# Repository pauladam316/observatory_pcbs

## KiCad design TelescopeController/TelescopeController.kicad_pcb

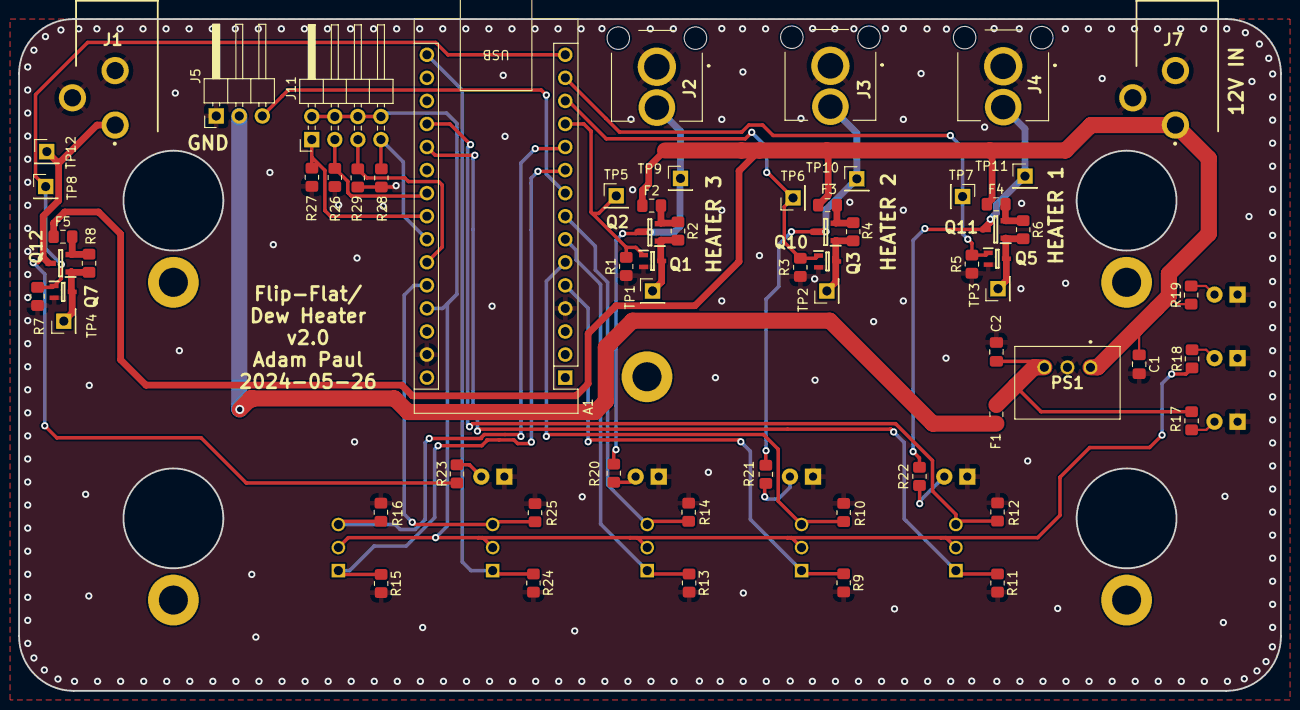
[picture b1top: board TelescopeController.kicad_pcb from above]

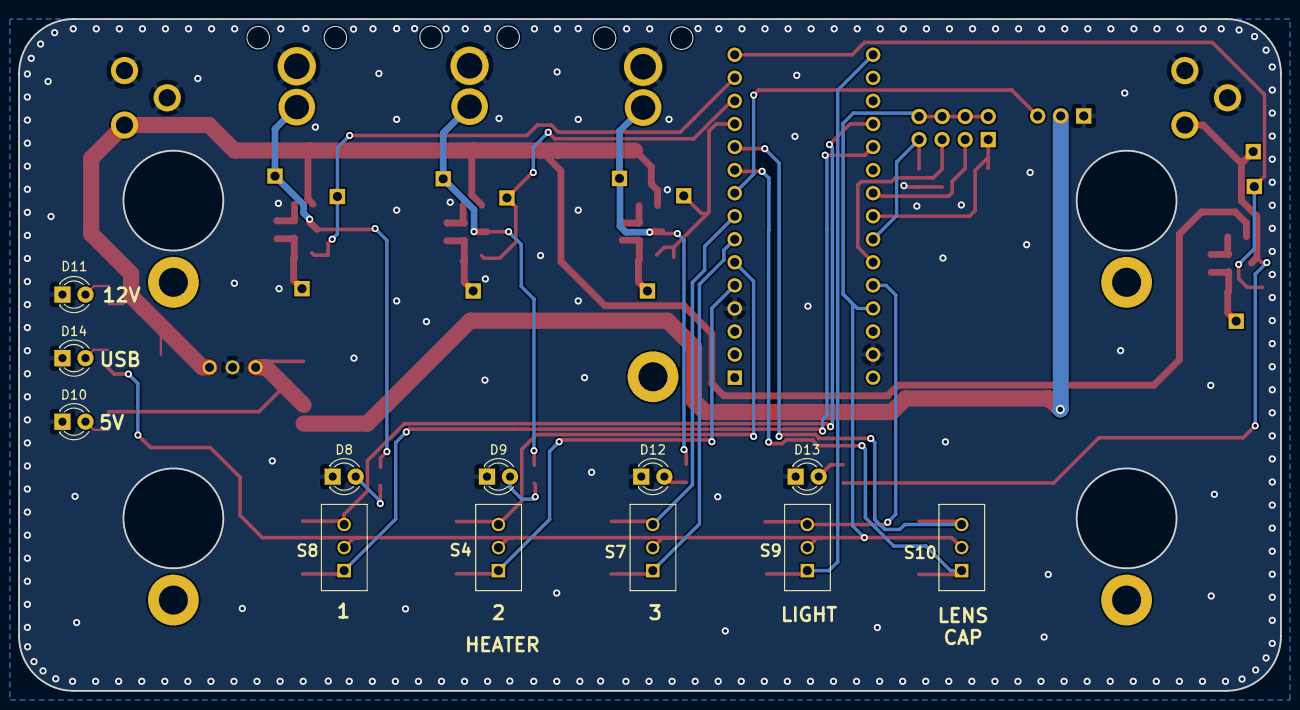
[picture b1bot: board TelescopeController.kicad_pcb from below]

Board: 2 copper layers, 139.0 x 74.0 mm, 77 parts (12 on the bottom side), 43 nets.

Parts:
A1: Arduino_Nano_v3.x; Arduino_Nano
C1: 10uF; C_0805_2012Metric_Pad1.18x1.45mm_HandSolder
C2: 22uF; C_0805_2012Metric_Pad1.18x1.45mm_HandSolder
D8, D9, D10, D11, D12, D13, D14: LED; LED_D3.0mm
F1: 1A; Fuse_0805_2012Metric_Pad1.15x1.40mm_HandSolder
F2, F3, F4, F5: 1.5A; Fuse_0805_2012Metric_Pad1.15x1.40mm_HandSolder
J1, J7: PJ-102BH; PJ-102AH
J2, J3, J4: RCJ-041; RCJ041
J5: Conn_01x03_Pin; PinHeader_1x03_P2.54mm_Horizontal
J11: Conn_02x04_Counter_Clockwise; PinHeader_2x04_P2.54mm_Horizontal
PS1: P78E05-1000; P78E051000
Q1, Q3, Q5, Q7: DMN63D8LW-13; SOT65P210X110-3N
Q2, Q10, Q11, Q12: DMP3099L-7; SOT96P240X115-3N
R1, R2, R3, R4, R5, R6, R7, R8, R9, R10, R11, R12, R13, R14, R15, R16, R19, R20, R21, R22, R23, R24, R25: 1k; R_0805_2012Metric_Pad1.20x1.40mm_HandSolder
R17, R18: 300R; R_0805_2012Metric_Pad1.20x1.40mm_HandSolder
R26, R27, R28, R29: 10k; R_0805_2012Metric_Pad1.20x1.40mm_HandSolder
S4, S7, S8, S9, S10: AS1E-2M-10-Z; AS1E2M10Z
TP1, TP2, TP3, TP4, TP5, TP6, TP7, TP8, TP9, TP10, TP11, TP12: TestPoint; PinHeader_1x01_P2.54mm_Vertical

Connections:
+5V: A1.27 (+5V), J11.2, J11.4, J11.6, J11.8, R18.1, S4.2, S7.2, S8.2, S9.2, S10.2
+12V: C1.1, F2.1, F3.1, F4.1, F5.1, J7.1, PS1.1 (+VIN), R19.1
/12V_SWITCHING1/IN: A1.13 (D10), Q3.1, R3.1, TP6.1
/12V_SWITCHING1/OUT: J3.2, Q10.3 (D), R21.1, TP10.1
/12V_SWITCHING2/IN: A1.14 (D11), Q5.1, R5.1, TP7.1
/12V_SWITCHING2/OUT: J4.2, Q11.3 (D), R22.1, TP11.1
/12V_SWITCHING3/IN: A1.15 (D12), Q7.1, R7.1, TP8.1
/12V_SWITCHING3/OUT: J1.1, Q12.3 (D), R23.1, TP12.1
/12V_SWITCHING/IN: A1.12 (D9), Q1.1, R1.1, TP5.1
/12V_SWITCHING/OUT: J2.2, Q2.3 (D), R20.1, TP9.1
/CAP_CLOSE: A1.11 (D8), R16.1, S10.3
/CAP_OPEN: A1.10 (D7), R15.1, S10.1
/HEATER1_OFF: A1.19 (A0), R12.1, S8.3
/HEATER1_ON: A1.20 (A1), R11.1, S8.1
/HEATER2_OFF: A1.6 (D3), R10.1, S4.3
/HEATER2_ON: A1.5 (D2), R9.1, S4.1
/HEATER3_OFF: A1.8 (D5), R14.1, S7.3
/HEATER3_ON: A1.7 (D4), R13.1, S7.1
/LIGHT_OFF: A1.26 (A7), R25.1, S9.3
/LIGHT_ON: A1.16 (D13), R24.1, S9.1
/Thermistor1/AOUT: A1.23 (A4), J11.1, R27.1
/Thermistor2/AOUT: A1.24 (A5), J11.7, R28.1
/Thermistor3/AOUT: A1.25 (A6), J11.5, R29.1
/Thermistor/AOUT: A1.22 (A3), J11.3, R26.1
GND: A1.4 (GND), A1.29 (GND), C1.2, C2.2, D8.1 (K), D9.1 (K), D10.1 (K), D11.1 (K), D12.1 (K), D13.1 (K), D14.1 (K), J1.2, J1.3, J2.1, J3.1, J4.1, J5.1, J7.2, J7.3, PS1.2 (GND), Q1.2, Q3.2, Q5.2, Q7.2, R1.2, R3.2, R5.2, R7.2, R9.2, R10.2, R11.2, R12.2, R13.2, R14.2, R15.2, R16.2, R24.2, R25.2, R26.2, R27.2, R28.2, R29.2
unnamed: A1.9 (D6), J5.3
unnamed: D8.2 (A), R22.2
unnamed: D9.2 (A), R21.2
unnamed: D10.2 (A), R17.2
unnamed: D11.2 (A), R19.2
unnamed: D12.2 (A), R20.2
unnamed: D13.2 (A), R23.2
unnamed: D14.2 (A), R18.2
unnamed: F1.2, J5.2
unnamed: C2.1, F1.1, PS1.3 (+VOUT), R17.1
unnamed: Q1.3, Q2.1 (G), R2.2, TP1.1
unnamed: F2.2, Q2.2 (S), R2.1
unnamed: Q3.3, Q10.1 (G), R4.2, TP2.1
unnamed: F3.2, Q10.2 (S), R4.1
unnamed: Q5.3, Q11.1 (G), R6.2, TP3.1
unnamed: F4.2, Q11.2 (S), R6.1
unnamed: Q7.3, Q12.1 (G), R8.2, TP4.1
unnamed: F5.2, Q12.2 (S), R8.1

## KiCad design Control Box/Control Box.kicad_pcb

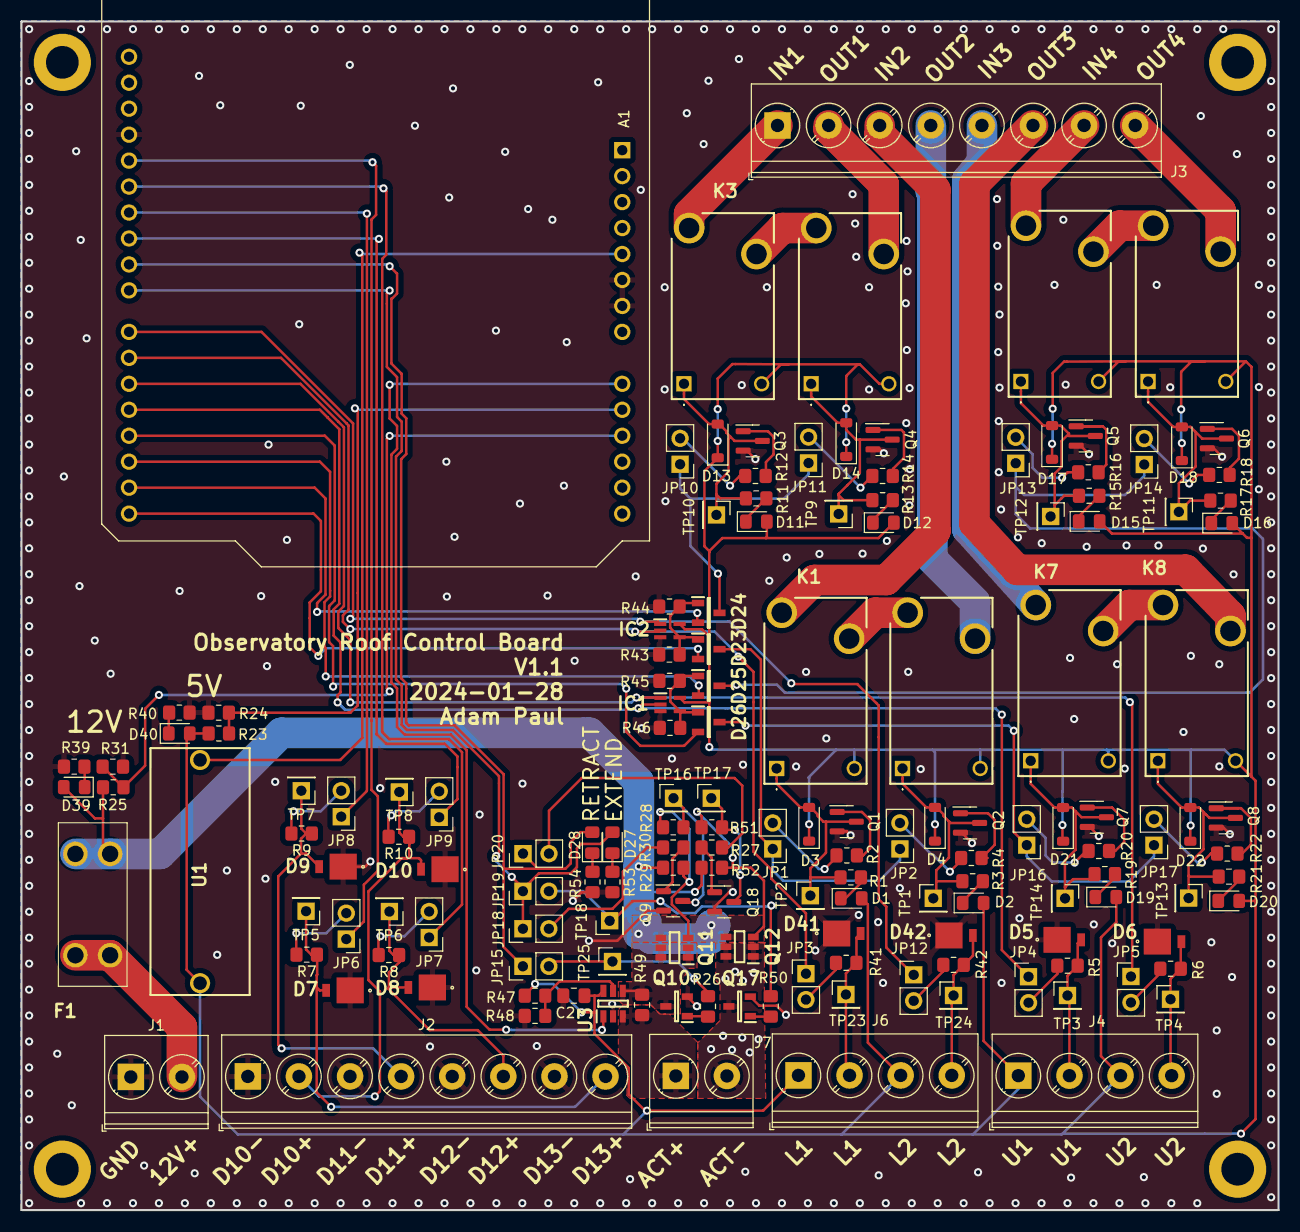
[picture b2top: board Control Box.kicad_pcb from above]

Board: 2 copper layers, 123.0 x 116.3 mm, 158 parts (0 on the bottom side), 108 nets.

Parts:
A1: Arduino_UNO_R3
C2: 0.1uF; C_0805_2012Metric_Pad1.18x1.45mm_HandSolder
D1, D2, D11, D12, D15, D16, D19, D20, D27, D28, D39, D40: LG R971-KN-1; LED_0805_2012Metric_Pad1.15x1.40mm_HandSolder
D3, D4, D13, D14, D17, D18, D21, D22: 1N4148W-TP; D_SOD-123
D5, D6, D7, D8, D9, D10, D41, D42: SMP5.0A-M3/84A; DO-220AA
D23, D24, D25, D26: DMG2305UX-13; SOT96P240X120-3N
F1: 3568
H1, H2, H3, H4: MountingHole; MountingHole_3.2mm_M3_DIN965_Pad
IC1, IC2: SN74LVC1G32DCKR; SOT65P210X110-5N
J1, J7: Screw_Terminal_01x02; TerminalBlock_Phoenix_PT-1,5-2-5.0-H_1x02_P5.00mm_Horizontal
J2, J3: Screw_Terminal_01x08; TerminalBlock_Phoenix_PT-1,5-8-5.0-H_1x08_P5.00mm_Horizontal
J4, J6: Screw_Terminal_01x04; TerminalBlock_Phoenix_PT-1,5-4-5.0-H_1x04_P5.00mm_Horizontal
JP1, JP2, JP3, JP4, JP5, JP6, JP7, JP8, JP9, JP10, JP11, JP12, JP13, JP14, JP15, JP16, JP17, JP18, JP19, JP20: Jumper; PinHeader_1x02_P2.54mm_Vertical
K1, K2, K3, K4, K5, K6, K7, K8: AHQSH105LM100G
Q1, Q2, Q3, Q4, Q5, Q6, Q7, Q8, Q9, Q18: MMBT3904; SOT-23
Q10, Q17: DMN2056U-7; SOT96P240X100-3N
Q11, Q12: SI3443CDV-T1-GE3; SOP95P284X110-6N
R1, R3, R11, R13, R15, R17, R19, R21, R40, R53, R54: 140R; R_0805_2012Metric_Pad1.20x1.40mm_HandSolder
R2, R4, R12, R14, R16, R18, R20, R22: 500R; R_0805_2012Metric_Pad1.20x1.40mm_HandSolder
R5, R6, R7, R8, R9, R10, R41, R42: 125R; R_0805_2012Metric_Pad1.20x1.40mm_HandSolder
R23, R24, R25, R47, R48: 10k; R_0805_2012Metric_Pad1.20x1.40mm_HandSolder
R26, R28, R43, R44, R45, R46, R50, R51: 1k; R_0805_2012Metric_Pad1.20x1.40mm_HandSolder
R27, R30: 2.2k; R_0805_2012Metric_Pad1.20x1.40mm_HandSolder
R29, R52: 4.7k; R_0805_2012Metric_Pad1.20x1.40mm_HandSolder
R31: 3k; R_0805_2012Metric_Pad1.20x1.40mm_HandSolder
R39: 490R; R_0805_2012Metric_Pad1.20x1.40mm_HandSolder
R49: 42m; R_0805_2012Metric_Pad1.20x1.40mm_HandSolder
TP1, TP2, TP3, TP4, TP5, TP6, TP7, TP8, TP9, TP10, TP11, TP12, TP13, TP14, TP16, TP17, TP18, TP23, TP24, TP25: TestPoint; PinHeader_1x01_P2.54mm_Vertical
U1: 4527
U3: INA181A1IDBVR; SOT95P280X145-6N

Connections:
+5V: C2.1, D1.2 (A), D2.2 (A), D3.1 (K), D4.1 (K), D11.2 (A), D12.2 (A), D13.1 (K), D14.1 (K), D15.2 (A), D16.2 (A), D17.1 (K), D18.1 (K), D19.2 (A), D20.2 (A), D21.1 (K), D22.1 (K), D40.2 (A), IC1.5 (VCC), IC2.5 (VCC), J4.1, J4.3, J6.1, J6.3, K1.2 (COIL_2), K2.2 (COIL_2), K3.2 (COIL_2), K4.2 (COIL_2), K5.2 (COIL_2), K6.2 (COIL_2), K7.2 (COIL_2), K8.2 (COIL_2), R23.2, R47.1, U1.1, U3.6 (VS)
+12V: D39.2 (A), F1.3, F1.4, Q11.4 (S), Q12.4 (S), R25.2, R29.2, R52.2
/GPIOProtection1/IN: A1.21 (D6), IC2.2 (B), JP3.1
/GPIOProtection1/OUT: D41.2, J6.2, R41.1, TP23.1
/GPIOProtection/IN: A1.19 (D4), IC1.2 (B), JP4.1
/GPIOProtection/OUT: D5.2, J4.2, R5.1, TP3.1
/H-Bridge/+OUT: J7.1, R49.2, U3.3 (IN+)
/H-Bridge/-OUT: J7.2, Q12.1 (D_1), Q12.2 (D_2), Q12.5 (D_3), Q12.6 (D_4), Q17.3 (D)
/H-Bridge/EXTEND: A1.23 (D8), D27.2 (A), JP18.1, JP19.1
/H-Bridge/RETRACT: A1.24 (D9), D28.2 (A), JP15.1, JP20.1
/H-Bridge/SENSE: A1.9 (A0), U3.1 (OUT)
/OR GATE1/A: A1.22 (D7), IC2.1 (A), JP12.1
/OR GATE1/Y: D23.1 (G), D24.1 (G), IC2.4 (Y), R43.1, R44.1
/OR GATE/A: A1.20 (D5), IC1.1 (A), JP5.1
/OR GATE/Y: D25.1 (G), D26.1 (G), IC1.4 (Y), R45.1, R46.1
/Relay/EN: A1.15 (D0/RX), D23.2 (S)
/Relay/IN: J3.3, K1.4 (NO)
/Relay/OUT: J3.4, K2.3 (COM)
/sheet651C9752/OUT: D6.2, J4.4, R6.1, TP4.1
/sheet651C9753/OUT: D42.2, J6.4, R42.1, TP24.1
/sheet652FCB77/EN: A1.16 (D1/TX), D24.2 (S)
/sheet652FCB77/IN: J3.1, K3.4 (NO)
/sheet652FCB77/OUT: J3.2, K4.3 (COM)
/sheet6528B80B/IN: A1.25 (D10), JP9.1
/sheet6528B80B/OUT: D10.2, J2.2, R10.1, TP8.1
/sheet65287DBB/IN: A1.26 (D11), JP8.1
/sheet65287DBB/OUT: D9.2, J2.4, R9.1, TP7.1
/sheet65300B6A/EN: A1.17 (D2), D25.2 (S)
/sheet65300B6A/IN: J3.7, K5.4 (NO)
/sheet65300B6A/OUT: J3.8, K6.3 (COM)
/sheet65304B89/EN: A1.18 (D3), D26.2 (S)
/sheet65304B89/IN: J3.5, K7.4 (NO)
/sheet65304B89/OUT: J3.6, K8.3 (COM)
/sheet652808C1/IN: A1.28 (D13), JP6.1
/sheet652808C1/OUT: D7.2, J2.8, R7.1, TP5.1
/sheet65284368/IN: A1.27 (D12), JP7.1
/sheet65284368/OUT: D8.2, J2.6, R8.1, TP6.1
GND: A1.6 (GND), A1.7 (GND), A1.29 (GND), C2.2, D5.1, D6.1, D7.1, D8.1, D9.1, D10.1, D41.1, D42.1, IC1.3 (GND), IC2.3 (GND), J1.1, J2.1, J2.3, J2.5, J2.7, Q1.2 (E), Q2.2 (E), Q3.2 (E), Q4.2 (E), Q5.2 (E), Q6.2 (E), Q7.2 (E), Q8.2 (E), Q9.2 (E), Q10.2 (S), Q17.2 (S), Q18.2 (E), R24.1, R31.1, R39.2, R40.2, R43.2, R44.2, R45.2, R46.2, R48.2, R53.2, R54.2, U3.2 (GND)
unnamed: A1.5 (+5V), U1.2
unnamed: A1.10 (A1), R23.1, R24.2
unnamed: A1.11 (A2), R25.1, R31.2
unnamed: D1.1 (K), R1.1
unnamed: D2.1 (K), R3.1
unnamed: D3.2 (A), K1.1 (COIL_1), Q1.3 (C), R1.2, TP2.1
unnamed: D4.2 (A), K2.1 (COIL_1), Q2.3 (C), R3.2, TP1.1
unnamed: D11.1 (K), R11.1
unnamed: D12.1 (K), R13.1
unnamed: D13.2 (A), K3.1 (COIL_1), Q3.3 (C), R11.2, TP10.1
unnamed: D14.2 (A), K4.1 (COIL_1), Q4.3 (C), R13.2, TP9.1
unnamed: D15.1 (K), R15.1
unnamed: D16.1 (K), R17.1
unnamed: D17.2 (A), K5.1 (COIL_1), Q5.3 (C), R15.2, TP12.1
unnamed: D18.2 (A), K6.1 (COIL_1), Q6.3 (C), R17.2, TP11.1
unnamed: D19.1 (K), R19.1
unnamed: D20.1 (K), R21.1
unnamed: D21.2 (A), K7.1 (COIL_1), Q7.3 (C), R19.2, TP14.1
unnamed: D22.2 (A), K8.1 (COIL_1), Q8.3 (C), R21.2, TP13.1
unnamed: D23.3 (D), JP1.1, JP2.1
unnamed: D24.3 (D), JP10.1, JP11.1
unnamed: D25.3 (D), JP13.1, JP14.1
unnamed: D26.3 (D), JP16.1, JP17.1
unnamed: D27.1 (K), R53.1
unnamed: D28.1 (K), R54.1
unnamed: D39.1 (K), R39.1
unnamed: D40.1 (K), R40.1
unnamed: F1.1, F1.2, J1.2
unnamed: JP1.2, R2.2
unnamed: JP2.2, R4.2
unnamed: JP3.2, R41.2
unnamed: JP4.2, R5.2
unnamed: JP5.2, R6.2
unnamed: JP6.2, R7.2
unnamed: JP7.2, R8.2
unnamed: JP8.2, R9.2
unnamed: JP9.2, R10.2
unnamed: JP10.2, R12.2
unnamed: JP11.2, R14.2
unnamed: JP12.2, R42.2
unnamed: JP13.2, R16.2
unnamed: JP14.2, R18.2
unnamed: JP15.2, R26.2, TP25.1
unnamed: JP16.2, R20.2
unnamed: JP17.2, R22.2
unnamed: JP18.2, R30.2
unnamed: JP19.2, R50.2, TP18.1
unnamed: JP20.2, R27.2
unnamed: K1.3 (COM), K2.4 (NO)
unnamed: K3.3 (COM), K4.4 (NO)
unnamed: K5.3 (COM), K6.4 (NO)
unnamed: K7.3 (COM), K8.4 (NO)
unnamed: Q1.1 (B), R2.1
unnamed: Q2.1 (B), R4.1
unnamed: Q3.1 (B), R12.1
unnamed: Q4.1 (B), R14.1
unnamed: Q5.1 (B), R16.1
unnamed: Q6.1 (B), R18.1
unnamed: Q7.1 (B), R20.1
unnamed: Q8.1 (B), R22.1
unnamed: Q9.1 (B), R30.1
unnamed: Q9.3 (C), R28.2, TP16.1
unnamed: Q10.3 (D), Q11.1 (D_1), Q11.2 (D_2), Q11.5 (D_3), Q11.6 (D_4), R49.1, U3.4 (IN-)
unnamed: Q10.1 (G), R26.1
unnamed: Q11.3 (G), R28.1, R29.1
unnamed: Q12.3 (G), R51.1, R52.1
unnamed: Q17.1 (G), R50.1
unnamed: Q18.1 (B), R27.1
unnamed: Q18.3 (C), R51.2, TP17.1
unnamed: R47.2, R48.1, U3.5 (REF)

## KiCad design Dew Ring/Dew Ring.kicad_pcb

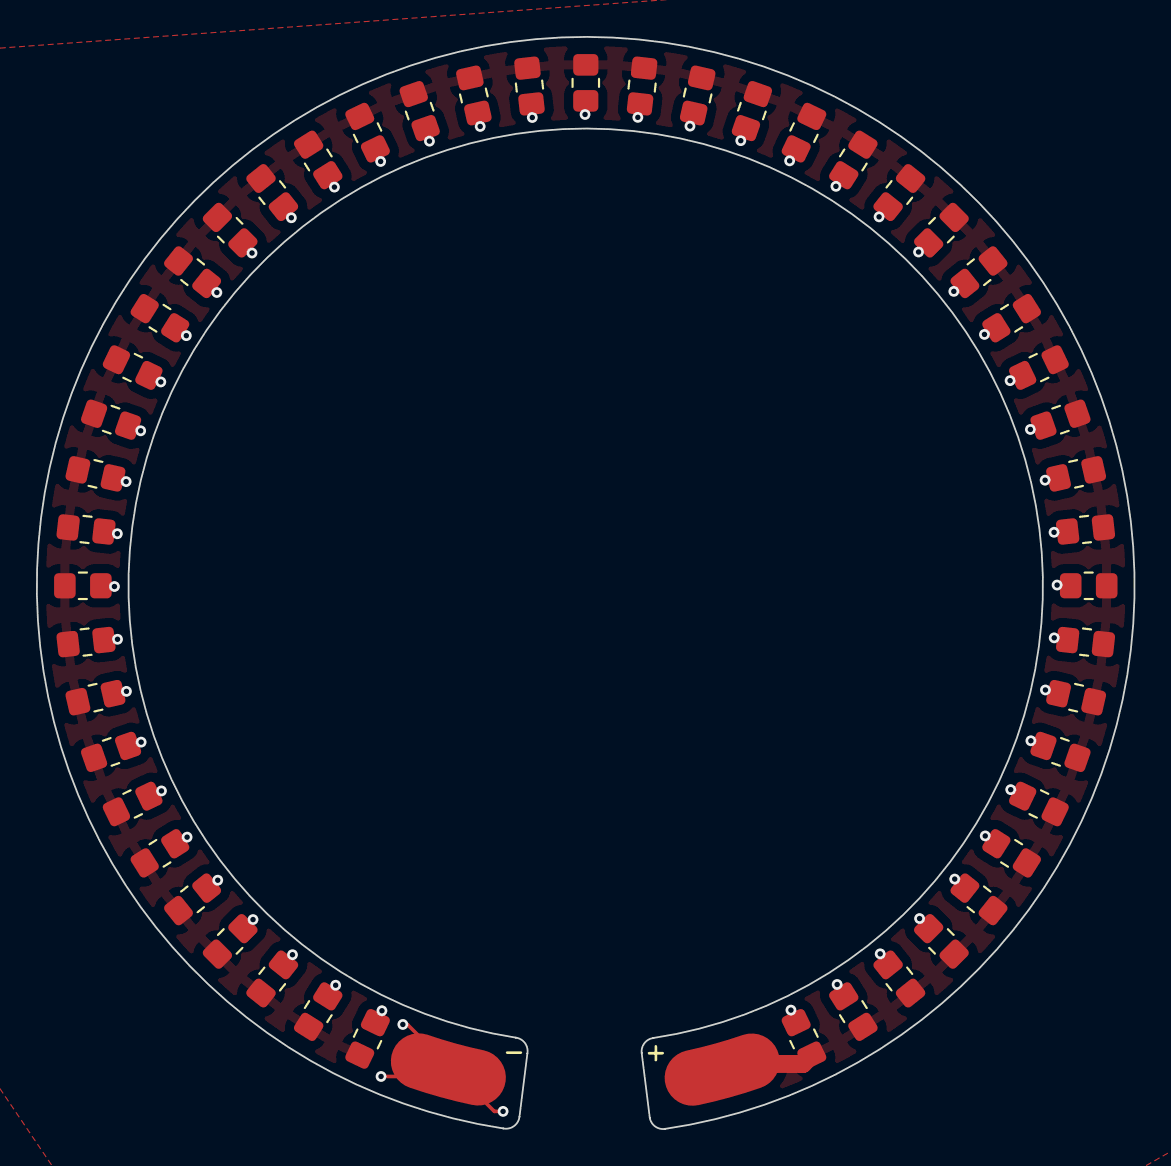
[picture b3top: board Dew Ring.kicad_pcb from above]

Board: 2 copper layers, 61.0 x 60.7 mm, 49 parts (0 on the bottom side), 2 nets.

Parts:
R1, R51, R52, R53, R54, R55, R56, R57, R58, R59, R60, R68, R69, R70, R71, R72, R73, R74, R75, R76, R77, R78, R79, R80, R81, R82, R83, R84, R85, R86, R87, R88, R89, R90, R91, R92, R93, R94, R95, R96, R97, R98, R99, R100, R101, R102, R103, R104, R105: 3.3k; R_0805_2012Metric_Pad1.20x1.40mm_HandSolder

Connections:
+12V: R1.1, R51.1, R52.1, R53.1, R54.1, R55.1, R56.1, R57.1, R58.1, R59.1, R60.1, R68.1, R69.1, R70.1, R71.1, R72.1, R73.1, R74.1, R75.1, R76.1, R77.1, R78.1, R79.1, R80.1, R81.1, R82.1, R83.1, R84.1, R85.1, R86.1, R87.1, R88.1, R89.1, R90.1, R91.1, R92.1, R93.1, R94.1, R95.1, R96.1, R97.1, R98.1, R99.1, R100.1, R101.1, R102.1, R103.1, R104.1, R105.1
GND: R1.2, R51.2, R52.2, R53.2, R54.2, R55.2, R56.2, R57.2, R58.2, R59.2, R60.2, R68.2, R69.2, R70.2, R71.2, R72.2, R73.2, R74.2, R75.2, R76.2, R77.2, R78.2, R79.2, R80.2, R81.2, R82.2, R83.2, R84.2, R85.2, R86.2, R87.2, R88.2, R89.2, R90.2, R91.2, R92.2, R93.2, R94.2, R95.2, R96.2, R97.2, R98.2, R99.2, R100.2, R101.2, R102.2, R103.2, R104.2, R105.2

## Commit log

2024-02-04 init commit
2024-05-25 change storeg
2024-05-27 add telescope controller v2
